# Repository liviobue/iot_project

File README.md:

# Information about the Project

## Python-Environment
Python 3.12.1

## Project-Structure
### Electronic:
- PCB-Designs
- Output für die Produktion
- Übersicht über die Board-Tests

### NodeRed
- Alle Flows in NodeRed

### Notebooks
- Jupyter Notebooks mit Prototyp-Code
- Jupyter Notebook mit vereinfachtem Code fürs Elektronik-Testing

### Presentation
- Vor-Präsentation
- Präsentation

### Service
- Information zum Service-File, um die Software automatisch beim Boot des Raspberry Pi's zu starten

### src/iot_project
- Code für die verschiedenen Teile der Software

## Get started manually:
### How to install
Execute this from the Repository-Root
```bash
pip install -e .
```

### How to run the sensor measurement only:
Create `.env`-file with `MONGO_URI` containing the connectionstring to your IoT-Database.
Then, run:
```bash
python -m iot_project.main
```

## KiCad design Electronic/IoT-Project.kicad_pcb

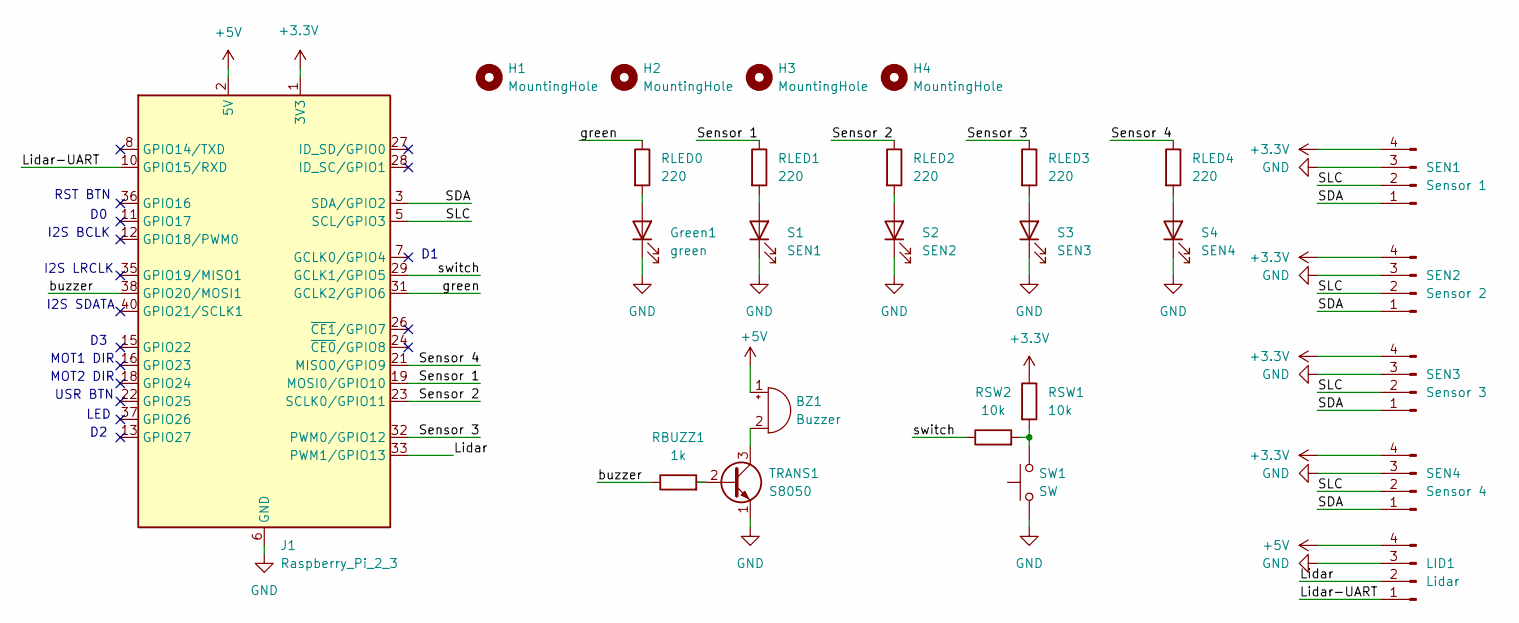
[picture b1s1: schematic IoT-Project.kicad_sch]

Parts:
BZ1: Buzzer; MagneticBuzzer_ProSignal_ABI-010-RC
Green1: green; LED_D5.0mm
H1, H2, H3, H4: MountingHole; MountingHole_2.7mm_M2.5
J1: Raspberry_Pi_2_3; PinHeader_2x20_P2.54mm_Vertical
LID1: Lidar; JST_PH_B4B-PH-K_1x04_P2.00mm_Vertical
RBUZZ1: 1k; R_Axial_DIN0207_L6.3mm_D2.5mm_P10.16mm_Horizontal
RLED0, RLED1, RLED2, RLED3, RLED4: 220; R_Axial_DIN0207_L6.3mm_D2.5mm_P10.16mm_Horizontal
RSW1, RSW2: 10k; R_Axial_DIN0207_L6.3mm_D2.5mm_P10.16mm_Horizontal
S1: SEN1; LED_D5.0mm
S2: SEN2; LED_D5.0mm
S3: SEN3; LED_D5.0mm
S4: SEN4; LED_D5.0mm
SEN1: Sensor 1; PinHeader_1x04_P2.54mm_Vertical
SEN2: Sensor 2; PinHeader_1x04_P2.54mm_Vertical
SEN3: Sensor 3; PinHeader_1x04_P2.54mm_Vertical
SEN4: Sensor 4; PinHeader_1x04_P2.54mm_Vertical
SW1: SW; SW_PUSH-12mm_Wuerth-430476085716
TRANS1: S8050; TO-92_Inline

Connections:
+3.3V: J1.1 (3V3), J1.17 (3V3), RSW1.1, SEN1.4, SEN2.4, SEN3.4, SEN4.4
+5V: BZ1.1 (+), J1.2 (5V), J1.4 (5V), LID1.4
/Lidar: J1.33 (PWM1/GPIO13), LID1.2
/Lidar-UART: J1.10 (GPIO15/RXD), LID1.1
/SDA: J1.3 (SDA/GPIO2), SEN1.1, SEN2.1, SEN3.1, SEN4.1
/SLC: J1.5 (SCL/GPIO3), SEN1.2, SEN2.2, SEN3.2, SEN4.2
/Sensor 1: J1.19 (MOSI0/GPIO10), RLED1.1
/Sensor 2: J1.23 (SCLK0/GPIO11), RLED2.1
/Sensor 3: J1.32 (PWM0/GPIO12), RLED3.1
/Sensor 4: J1.21 (MISO0/GPIO9), RLED4.1
/buzzer: J1.38 (GPIO20/MOSI1), RBUZZ1.1
/green: J1.31 (GCLK2/GPIO6), RLED0.1
/switch: J1.29 (GCLK1/GPIO5), RSW2.1
GND: Green1.1 (K), J1.6 (GND), J1.9 (GND), J1.14 (GND), J1.20 (GND), J1.25 (GND), J1.30 (GND), J1.34 (GND), J1.39 (GND), LID1.3, S1.1 (K), S2.1 (K), S3.1 (K), S4.1 (K), SEN1.3, SEN2.3, SEN3.3, SEN4.3, SW1.1, TRANS1.1 (E)
unnamed: BZ1.2 (-), TRANS1.3 (C)
unnamed: Green1.2 (A), RLED0.2
unnamed: RSW1.2, RSW2.2, SW1.2
unnamed: RLED1.2, S1.2 (A)
unnamed: RLED2.2, S2.2 (A)
unnamed: RLED3.2, S3.2 (A)
unnamed: RLED4.2, S4.2 (A)
unnamed: RBUZZ1.2, TRANS1.2 (B)

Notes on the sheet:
MOT2 DIR
MOT1 DIR
I2S BCLK
USR BTN
LED
I2S LRCLK
I2S SDATA
RST BTN

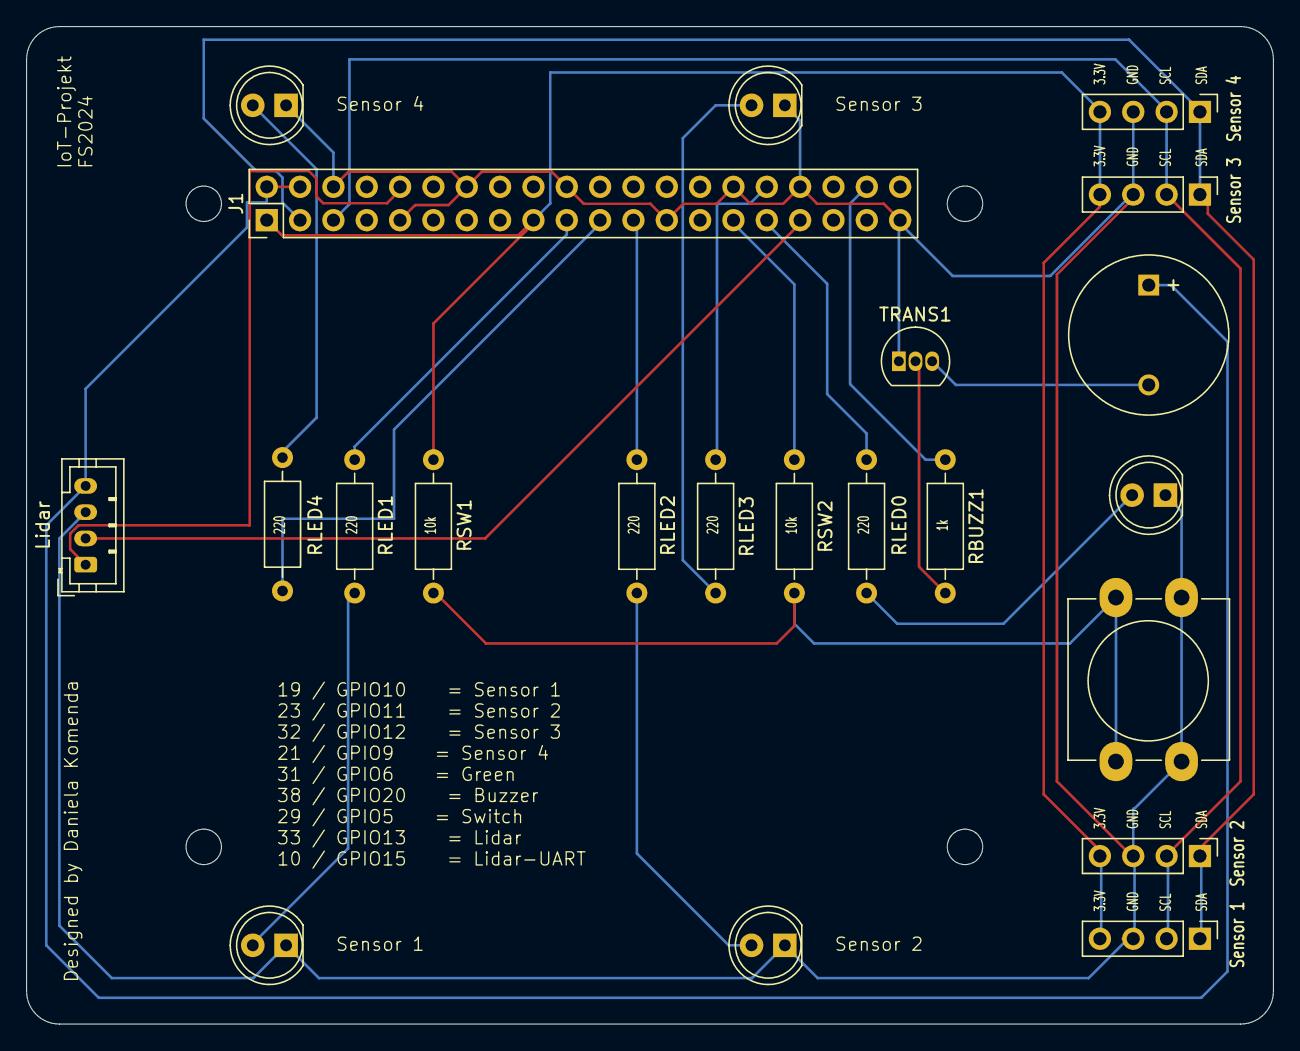
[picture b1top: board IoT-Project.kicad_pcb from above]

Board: 2 copper layers, 95.0 x 76.0 mm, 26 parts (0 on the bottom side), 22 nets.

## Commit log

2024-02-26 added readme
2024-03-03 Jupyter Notebook
2024-03-03 updated MAC-address
2024-03-24 started implementing MultiSensorClass
2024-03-25 Started implementing Button
2024-04-08 MultiGas-Sensor-ohne Cloud implemented
2024-04-08 MultiGas-Sensor-mitCloud: started implementing
2024-04-08 bug fixes in MultiGas-Sensor-ohneCloud
2024-04-12 add frontend folder
2024-04-12 added thingsboard setup files
2024-04-14 First approach to create a script
2024-04-14 project-refactoring
2024-04-15 edit gitignore
2024-04-22 add NodeRed Setup
2024-04-28 Added präsentations template
2024-05-06 get data from mongodb
2024-05-11 starting dashboard
2024-05-13 add flow which is working
2024-05-13 add other flow
2024-05-21 adapting UI
2024-05-21 changing dashboard design
2024-05-21 upstyle dashboard
2024-05-22 Zahlen runden
2024-05-25 Presentation
2024-05-25 renaming
2024-05-25 started with Python-Script
2024-05-25 refactoring sensor-software
2024-05-25 bug fixes
2024-05-25 refactoring, picar-controller
2024-05-25 Picar-Steering
2024-05-25 adjustment in README-File
2024-05-25 changes in .gitignore
2024-05-25 moved Notebooks
2024-05-25 move unused präsi
2024-05-25 update präsi
2024-05-25 adding message flow
2024-05-25 uploading seperate dashboard flow
2024-05-25 remove unused files
2024-05-25 changes in the presentation
2024-05-26 Paesentation weiterarbeiten
2024-05-26 Weiterarbeit an der Präsentation
2024-05-26 changing präsi
2024-05-27 changes in gitignore and requirements.txt
2024-05-27 Changes in the Notebooks
2024-05-27 bug fix
2024-05-27 improvement in error-handling
2024-05-27 Changing in TESTING-Notebook
2024-05-28 Changes in the gas_monitoring_system and Board-Tests
2024-05-28 Vorbereitung für finale Abgabe
2024-05-28 Service-File
2024-05-28 Monkey-Patch Picarx
2024-05-28 Autostart Software fixed and documented
2024-05-29 Shorter Aggregation
2024-05-29 adding new flows
2024-05-29 new flow
2024-05-29 Änderungen in der Präsentation
2024-05-29 new präsi
2024-05-30 added mail stuff
2024-05-31 adding mail flow
2024-05-31 changes on präsi
2024-05-31 changes in text
2024-06-01 changes in präsi
2024-06-02 new changes in präsi
2024-06-02 new changes in präsentation
2024-06-03 Präsentation für die Abgabe
